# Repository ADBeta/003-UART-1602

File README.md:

# 003-UART-1602
UART/RS232 Enabled controller for a basic `1602 Monochrome LCD`, in 4-bit mode
using the `CH32V003 - TSSOP-20` MCU  
Features:
* Selectable Baudrate
* Backlight Control using UART or Hardware override
* 4-bit LCD Control protocol support
* Automatic Line Scroll
* Operation down to 2.7v
* LCD Contrast Charge Pump
* Advance Display Control over UART

<div style="display: flex; align-items: center; gap: 10px;">
  <br>

</div>

## Display Operation
The display will read any incoming UART or RS232 Data and print it to the 
screen in realtime - If the edge of the screen is exceeded, the display will
drop incoming data.  
When `Line Feed` is received, and the Display is already on `Line 2`, the display
will Scroll Down, so the line being printed to remains as `Line 2`  

See [Control Characters](#control-characters) for a list of control commands
that can be used for the display

## Startup Conditions
When the Display is powered on, and before it receives any UART data, the
device is in the following state:
* LCB Backlight OFF
* Display Configured and blanked

## Selectable Baudrate
Receiver Baudrate is selected via the DIP-Switches onboard.  
The setting is checked once a second so the setting can be 
changed on the fly.  
```
B1 B0  Baud
0  0   4800
0  1   9600
1  0   115200
1  1   460800
```

## Low Voltage Operation
There is a negative charge pump onboard that provides a near-rail negative
voltage, that is fed to one end of the contrast selection Potentiometer.  
These LCDs are only officially rated at 5v, so use lower voltages 
**AT  YOUR OWN RISK**.  
To disable the charge pump, do not populate the components, and short
the `JMP_V0` Jumper.  
The `Minimum Voltage` for the unit is 2.7v

## Control Characters
`BELL    0x07` - Flashes the Backlight quickly for 3 Seconds  
`LF      0x0A` - Feeds line down, keeping Column Position  
`CR      0x0D` - Returns to the First Column on the current line  
`DC1     0x11` - Device Control 1, Turns Backlight On  
`DC2     0x12` - Device Control 2, Turns Backlight Off  
`DC3     0x13` -   
`DC4     0x14` -  
`ESCAPE  0x1B` - Clears the Screen and returns to position 0,0  

Any Control Characters not mentioned above will be ignored.

## Pinout
```
PA1  Baud Select 1
PA2  Baud Select 2

PC0  ---
PC1  LCD_RS  Register Select
PC2  LCD_RW  Read/Write
PC3  LCD_EN  Enable
PC4  LCD_D4  Display Data Pin 4
PC5  LCD_D5  Display Data Pin 5
PC6  LCD_D6  Display Data Pin 6
PC7  LCD_D7  Display Data Pin 7

PD0  Backlight Control
PD1  !!Reserved for SWIO!!
PD2  --
PD3  --
PD4  Charge Pump PWM
PD5  TX  UART Transmit (Not Connected)
PD6  RX  UART Receive
PD7  Reserved for NRST
```

## MkII PCB Partslist
```
C1    0603 1uF 10V
C2    0603 1uF 10V
C3    0603 1uF 10V
R1    0603 4K7
R2    100K 5mm x 5mm Potentiometer
D1    BAT54S
Q1    AO3401 P-Ch
Q2    A03400 N-Ch
U1    CH32V003
SW1   1.27mm 2P DIP Switch
```

## TODO
* Device Contol 3 and 4 Behaviour

----
ADBeta (c) 2024 - 2025

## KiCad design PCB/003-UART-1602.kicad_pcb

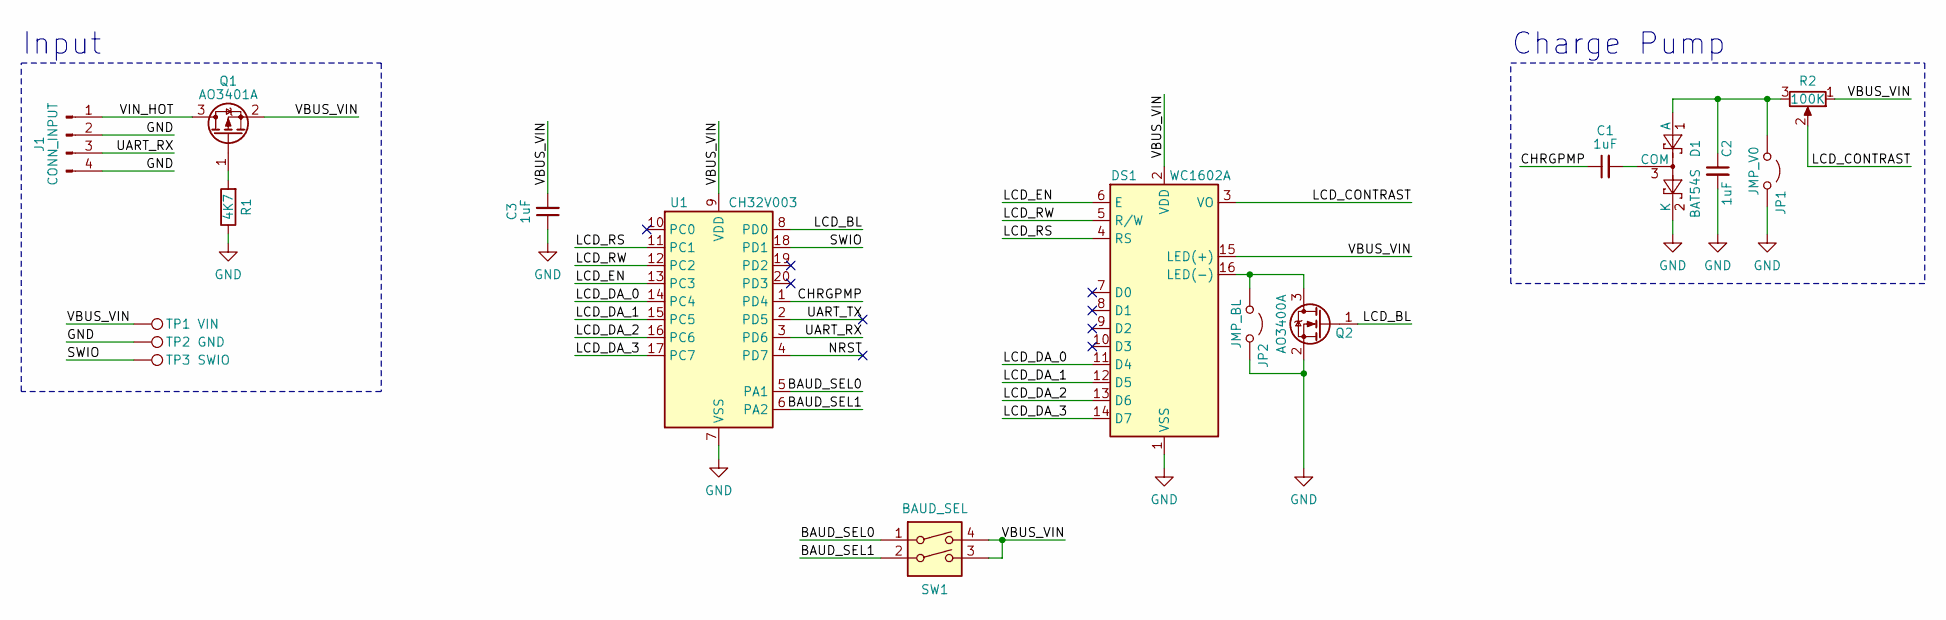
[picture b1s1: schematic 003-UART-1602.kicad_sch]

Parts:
C1, C2, C3: 1uF; C_0805_2012Metric
D1: BAT54S; SOT-23
DS1: WC1602A; PinHeader_1x16_P2.54mm_Vertical
J1: CONN_INPUT; PinHeader_1x04_P2.54mm_Vertical
JP1: JMP_V0; SolderJumper-2_P1.3mm_Open_RoundedPad1.0x1.5mm
JP2: JMP_BL; SolderJumper-2_P1.3mm_Open_RoundedPad1.0x1.5mm
Q1: AO3401A; SOT-23
Q2: AO3400A; SOT-23
R1: 4K7; R_0805_2012Metric
R2: 100K; Potentiometer_Piher_PT-6-V_Vertical
SW1: BAUD_SEL; SW_DIP_SPSTx02_Slide_Copal_CHS-02B_W7.62mm_P1.27mm
TP1: VIN; TestPoint_Pad_D1.0mm
TP2: GND; TestPoint_Pad_D1.0mm
TP3: SWIO; TestPoint_Pad_D1.0mm
U1: CH32V003; TSSOP-20_4.4x6.5mm_P0.65mm

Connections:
/BAUD_SEL0: SW1.1, U1.5 (PA1)
/BAUD_SEL1: SW1.2, U1.6 (PA2)
/CHRGPMP: C1.1, U1.1 (PD4)
/LCD_BL: Q2.1 (G), U1.8 (PD0)
/LCD_CONTRAST: DS1.3 (VO), R2.2
/LCD_DA_0: DS1.11 (D4), U1.14 (PC4)
/LCD_DA_1: DS1.12 (D5), U1.15 (PC5)
/LCD_DA_2: DS1.13 (D6), U1.16 (PC6)
/LCD_DA_3: DS1.14 (D7), U1.17 (PC7)
/LCD_EN: DS1.6 (E), U1.13 (PC3)
/LCD_RS: DS1.4 (RS), U1.11 (PC1)
/LCD_RW: DS1.5 (R/W), U1.12 (PC2)
/NRST: U1.4 (PD7)
/SWIO: TP3.1, U1.18 (PD1)
/UART_RX: J1.3, U1.3 (PD6)
/UART_TX: U1.2 (PD5)
/VBUS_VIN: C3.2, DS1.2 (VDD), DS1.15 (LED(+)), Q1.2 (S), R2.1, SW1.3, SW1.4, TP1.1, U1.9 (VDD)
/VIN_HOT: J1.1, Q1.3 (D)
GND: C2.2, C3.1, D1.2 (K), DS1.1 (VSS), J1.2, J1.4, JP1.1 (A), JP2.1 (A), Q2.2 (S), R1.1, TP2.1, U1.7 (VSS)
unnamed: C2.1, D1.1 (A), JP1.2 (B), R2.3
unnamed: C1.2, D1.3 (COM)
unnamed: DS1.16 (LED(-)), JP2.2 (B), Q2.3 (D)
unnamed: Q1.1 (G), R1.2

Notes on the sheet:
Charge Pump
Input

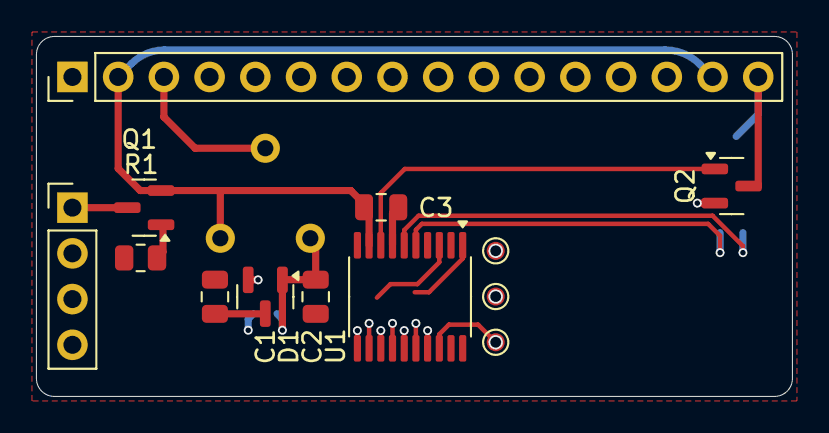
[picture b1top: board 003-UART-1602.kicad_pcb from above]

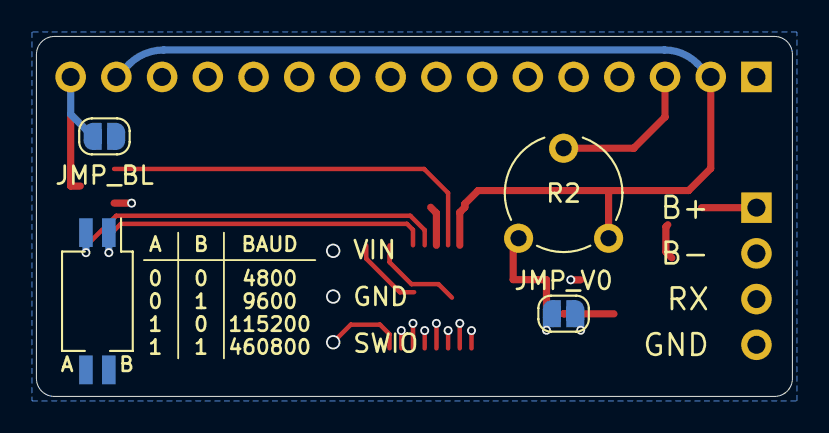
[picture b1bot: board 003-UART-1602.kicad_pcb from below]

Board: 2 copper layers, 42.0 x 20.0 mm, 17 parts (4 on the bottom side), 21 nets.

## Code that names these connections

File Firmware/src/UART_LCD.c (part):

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//#include <stdio.h>

/*** Pin Definitions *********************************************************/
#define PUMP_PWM     GPIO_PD4
#define LCD_BL       GPIO_PD0
#define BAUD_SEL0    GPIO_PA1
#define BAUD_SEL1    GPIO_PA2

/*** Macros ******************************************************************/
#define SYSTICK_ONE_MILLISECOND ((uint32_t)FUNCONF_SYSTEM_CORE_CLOCK / 1000)
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
// Create LCD Device
static lcd_device_t g_lcd_dev = {
	.LCD_RS      = GPIO_PC1,
	.LCD_RW      = GPIO_PC2,
	.LCD_EN      = GPIO_PC3,
	.LCD_DA      = {GPIO_PC4, GPIO_PC5, GPIO_PC6, GPIO_PC7},
};

lcd_position_t g_lcd_pos = {0, 0};
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__attribute__((interrupt))
void SysTick_Handler(void);

/// @brief Initialises PWM on Timer2,         NOTE: PD4 in this case
/// @param None
/// @return None
void pwm_init(void);
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	SystemInit();

	// Backlight is output, turn off by default
	gpio_set_mode(LCD_BL, OUTPUT_10MHZ_PP);
	gpio_digital_write(LCD_BL, GPIO_LOW);
	// Selection Switches are input
	gpio_set_mode(BAUD_SEL0, INPUT_PULLDOWN);
	gpio_set_mode(BAUD_SEL1, INPUT_PULLDOWN);
	// Charge Pump is output in alternate function mode for PWM
	gpio_set_mode(PUMP_PWM, OUTPUT_10MHZ_PP | OUTPUT_PP_AF);

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	Delay_Ms(250);
	lcd_init(&g_lcd_dev);

	// Start the PWM on PD4: 50% Duty, 9.9KHz
	pwm_init();
	pwm_set_duty(127);

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		{
			// Get the current Baud Setting selection
			uint8_t baud_setting = 
				((uint8_t)gpio_digital_read(BAUD_SEL1)) << 1 |
				 (uint8_t)gpio_digital_read(BAUD_SEL0);

			// Set the Baudrate register
			USART1->BRR = g_baud_lookup[baud_setting];
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
		if(g_systick_millis - g_last_light_update_millis > LIGHT_UPDATE_MS)
		{
			gpio_digital_write(LCD_BL, g_backlight_state);

			g_last_light_update_millis = g_systick_millis;
		} // End of Backlight Update
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
void pwm_init(void)
{
	// NOTE: Uses TIM2 Channel 1 (PD0) as the PWM Output pin
	// Change CHCTLR1 to CHCTLR2 for CH3 or CH4

	// Enable TIM2 Clock
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
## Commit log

2024-12-07 Init sequence finished
2024-12-07 Added Basic UART Control
2024-12-07 Updated TODO
2024-12-07 Updated UART Code
2024-12-09 Added BAUD Setting detection
2024-12-10 Added reverse protection to test & connectors
2024-12-11 Added some special character support
2024-12-11 Changed parsing flow
2024-12-11 Removed RS232 Option
2024-12-12 Fixed baud detection - Added Read CHAR from LCD Memory
2024-12-12 Updated PCB
2024-12-13 Ver 1.0 Release
2024-12-15 Tidied up LF code
2024-12-16 PCB Progress
2024-12-16 Changed Project Name
2024-12-17 Added DIP Switch to PCB
2024-12-17 Almost Final PCB
2024-12-18 PCB Finished
2024-12-18 Added Images
2024-12-18 Changed Image sizes
2024-12-30 MkII PCB Notes
2024-12-30 Added BELL Command
2025-01-01 MkII PCB Design started
2025-01-01 Updated version and copyright date
